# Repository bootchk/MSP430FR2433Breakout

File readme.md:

MSP430FR2433Breakout

A breakout board for Texas Instrument's MSP430FR2433 embedded microprocessor with Abracon RTC.

Features:

     small size
     nano power
     on board RTC to wake the MCU from deep sleep
     Tag Connect programming connector

Shared at OSHPark.  Not tested yet.

### Use case

You use a Launchpad and other breakout boards for development.
Your other breakout boards are small but the Launchpad is not.
You need a smaller version of the Launchpad.

While you can cut the Launchpad in two along its dotted line, that still leaves a 25 square centimeter board.
If weight and size are a concern, you need a smaller MSP430 breakout board.

You also want to use the MCU in low power mode LPM4.5
but you don't have an external wake up interrupt.
So you need an on board RTC to wake the MCU.

In other words, this board is a tiny motherboard with clock, for nano power applications.
You add a power supply and peripherals.

### Nano power

The use case is that the MCU sleeps mostly but wakes itself periodically.

In LPM 3 or LPM3.5, the RTC internal to the MCU wakes the MCU.
Current draw in those modes is on the order of 700nA.

To get even lower current draw, you need to use LPM4.5 with an external wakeup.
Current draw in LPM4.5 mode (with SVS disabled) is on the order of 16nA.
An external Abracon RTC to wake the MCU draws only about 25nA.
Thus the board can operate at an average current of about 50 nA.

(When SVS is disabled, you must consider what happens on brownout.
If brownout occurs, the power supply may need to discharge completely
before a proper reset occurs.
LPM4.5 with SVS enabled draws about 250nA.)

### Peripherals on board

The board has no buttons (not a reset button) or LED's

The board has an on-board external RTC.
If you don't need it, just do not populate it.
You don't need it if you don't need nano power features and can use the RTC internal to the MCU,
or you have another external interrupt.

All other peripherals such as sensors will need to be external breakout boards.

### Power

Power can be a battery.
The MSP430FR2433 MCU accepts unregulated voltage from 1.9-3.6V.

I use an energy harvesting power board and a supercapacitor.

### Pinout

The MCU has 24 pins but only 23 distinct pins (Vss is duplicated.)

Of those 23, 21 are routed to jumpers.
NotReset and Test pins are routed to the Tag Connect connector for programming by Spy By Wire (SBW.)

Three pins (P1.1, P1.2, and P1.3)
are routed to a jumper but also routed as an I2C bus and interrupt to the Abracon RTC.
If you don't populate the RTC, and don't need an I2C bus, you can use those pins for other purposes.

Jumper pins are labeled with the primary function of GPIO pins e.g. P1.0.
If you use the GPIO pins for their secondary functions, you must mentally translate the names.

The jumper pins are ordered in numerical order of name i.e. P1.0 to P3.2.
Contrast to the LaunchPad, whose pins are arranged to fit a BoosterPack standard.

### Manufacturability

In my experience, you can reliably build the board at home using a stencil for low temp solder paste and a toaster oven for reflow.

If your soldering iron tip is fine enough, you might be able to retouch some of the MCU pins.
But the footprint is NOT a hand-solderable type (with pads extending farther from the chip.)

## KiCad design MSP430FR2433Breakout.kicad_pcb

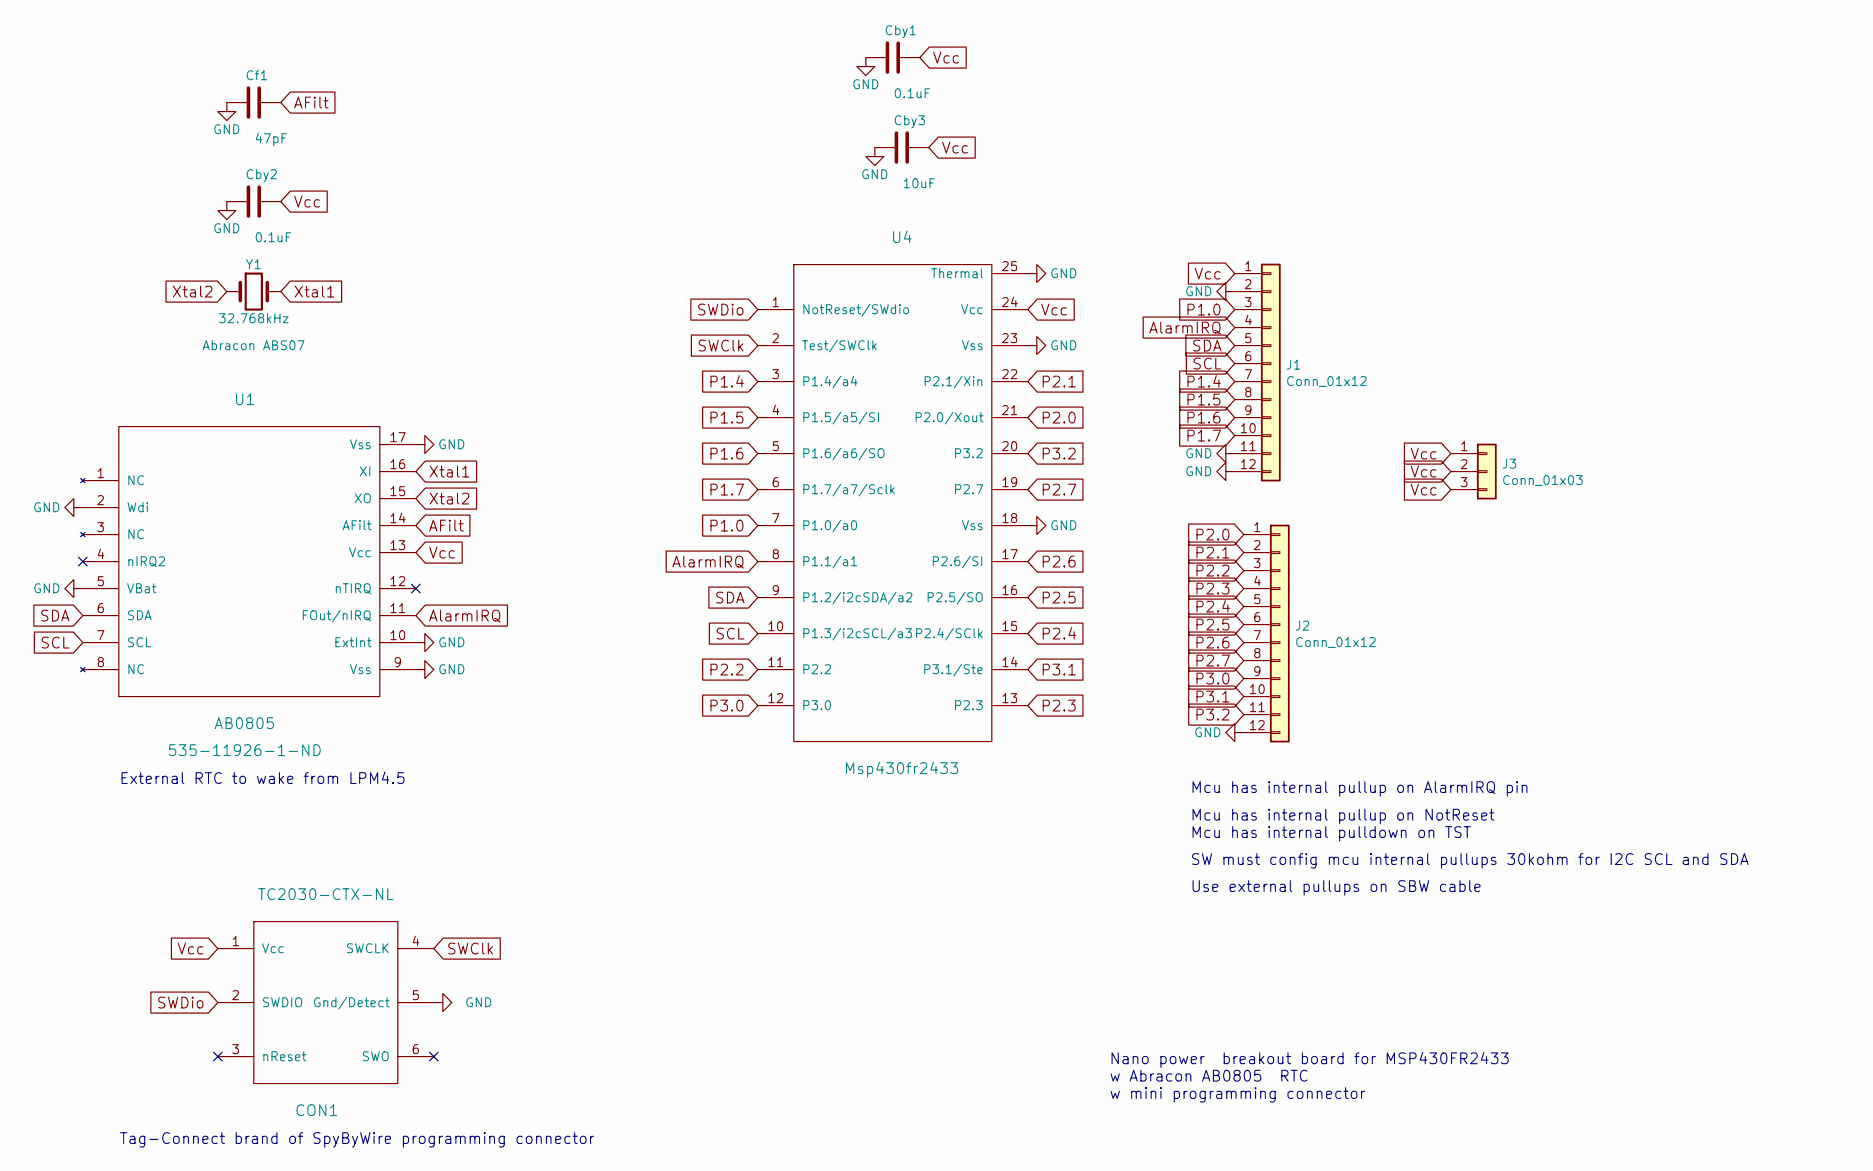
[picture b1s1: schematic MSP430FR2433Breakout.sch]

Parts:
CON1: TC2030-CTX-NL
Cby1, Cby2: 0.1uF; C_0603_1608Metric
Cby3: 10uF; C_0603_1608Metric
Cf1: 47pF; C_0603_1608Metric
J1, J2: Conn_01x12; PinHeader_1x12_P2.54mm_Vertical
J3: Conn_01x03; PinHeader_1x03_P2.54mm_Vertical
U1: AB0805; QFN-16-1EP_3x3mm_P0.5mm_EP1.75x1.75mm
U4: Msp430fr2433; QFN-24-1EP_4x4mm_P0.5mm_EP2.7x2.7mm_ThermalVias
Y1: 32.768kHz; Crystal_SMD_3215-2Pin_3.2x1.5mm

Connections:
AFilt: Cf1.1, U1.14 (AFilt)
AlarmIRQ: J1.4, U1.11 (FOut/nIRQ), U4.8 (P1.1/a1)
GND: CON1.5 (Gnd/Detect), Cby1.2, Cby2.2, Cby3.2, Cf1.2, J1.2, J1.11, J1.12, J2.12, U1.2 (Wdi), U1.5 (VBat), U1.9 (Vss), U1.10 (ExtInt), U1.17 (Vss), U4.18 (Vss), U4.23 (Vss), U4.25 (Thermal)
P1.0: J1.3, U4.7 (P1.0/a0)
P1.4: J1.7, U4.3 (P1.4/a4)
P1.5: J1.8, U4.4 (P1.5/a5/SI)
P1.6: J1.9, U4.5 (P1.6/a6/SO)
P1.7: J1.10, U4.6 (P1.7/a7/Sclk)
P2.0: J2.1, U4.21 (P2.0/Xout)
P2.1: J2.2, U4.22 (P2.1/Xin)
P2.2: J2.3, U4.11 (P2.2)
P2.3: J2.4, U4.13 (P2.3)
P2.4: J2.5, U4.15 (P2.4/SClk)
P2.5: J2.6, U4.16 (P2.5/SO)
P2.6: J2.7, U4.17 (P2.6/SI)
P2.7: J2.8, U4.19 (P2.7)
P3.0: J2.9, U4.12 (P3.0)
P3.1: J2.10, U4.14 (P3.1/Ste)
P3.2: J2.11, U4.20 (P3.2)
SCL: J1.6, U1.7 (SCL), U4.10 (P1.3/i2cSCL/a3)
SDA: J1.5, U1.6 (SDA), U4.9 (P1.2/i2cSDA/a2)
SWClk: CON1.4 (SWCLK), U4.2 (Test/SWClk)
SWDio: CON1.2 (SWDIO), U4.1 (NotReset/SWdio)
Vcc: CON1.1 (Vcc), Cby1.1, Cby2.1, Cby3.1, J1.1, J3.1, J3.2, J3.3, U1.13 (Vcc), U4.24 (Vcc)
Xtal1: U1.16 (XI), Y1.2
Xtal2: U1.15 (XO), Y1.1

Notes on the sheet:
Mcu has internal pullup on AlarmIRQ pin
Mcu has internal pullup on NotReset Mcu has internal pulldown on TST
SW must config mcu internal pullups 30kohm for I2C SCL and SDA
Nano power breakout board for MSP430FR2433 w Abracon AB0805 RTC w mini programming connector
Use external pullups on SBW cable
External RTC to wake from LPM4.5
Tag-Connect brand of SpyByWire programming connector

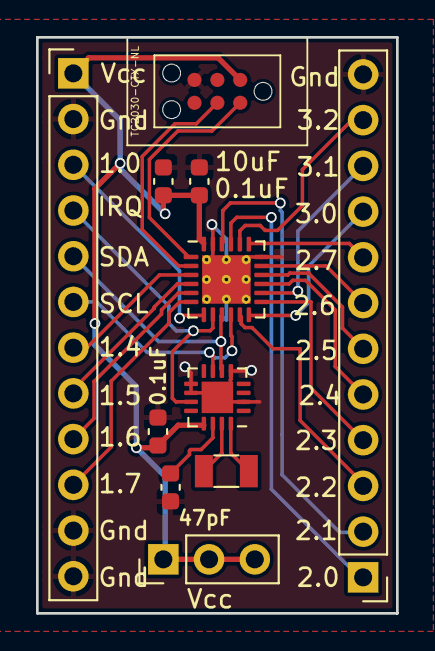
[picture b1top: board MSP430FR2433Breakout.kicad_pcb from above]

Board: 2 copper layers, 20.0 x 32.0 mm, 11 parts (0 on the bottom side), 26 nets.
